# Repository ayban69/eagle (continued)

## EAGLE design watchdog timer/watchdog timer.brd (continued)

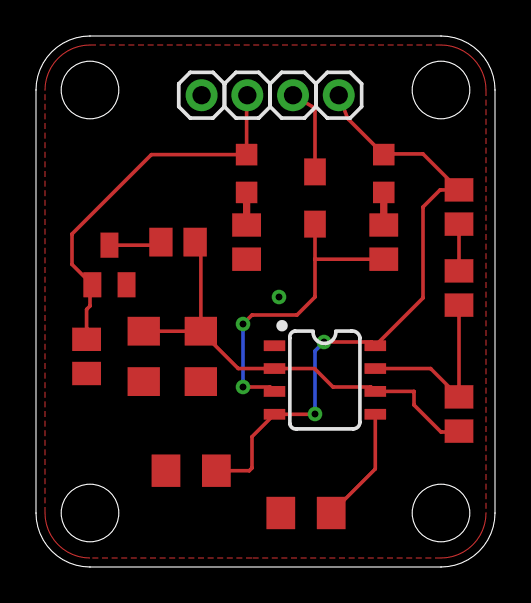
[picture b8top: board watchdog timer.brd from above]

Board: 2 copper layers, 25.5 x 29.5 mm, 21 parts (1 on the bottom side), 12 nets.

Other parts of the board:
U$1: ADILOGO

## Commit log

2018-01-17 seeeduino
2018-03-26 big 7 segment display
2018-03-27 new desing and simulate 7 segment
2018-03-28 new simulate big 7 segment
2018-04-03 big7segment with sec board layout
2018-04-03 separate sec to 7 segment boards
2018-04-21 arduino m0 pro
2018-04-30 added cable color description
2018-05-07 thicker big segment 7 sec
2018-10-12 adding 7 segment display stop mask cutout
